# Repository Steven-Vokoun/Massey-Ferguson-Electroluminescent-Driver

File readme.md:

# Massey Ferguson Electroluminescent Driver
Based upon the Steve Pietkiewicz of LTC Electroluminescent Panel Power Supply in [Linear Technology Application Note 61](https://www.analog.com/media/en/technical-documentation/application-notes/an61fa.pdf) August 1994
Project never long term tested due to only having one Electroluminescent gauge left on the tractor which was cloudy so just decided to use 12V modern gauges.  Thought more were EL gauges, but they were just burned out 12v lamps.  Simply completed this to learn Kicad with a usedful project before moving on to more complex things.

## Features
- Adjustable Voltage and Frequency
> After searching everything on line could not find the specifications for this old of a tractor so made sure it was adjustable to fine tune brightness.
- Square wave output centered around 0
- Case with mounting points for zip ties
> Ended up mounting it to the vibration dampening mount that the voltage regulator was previously on.  Tractor has a internally regulated alternator so it was no longer needed.  It could also be attached to the bolt pattern on the existing EL driver instead.

## Known Issues
- +5V pin of the 555 timer not routed.  Fixed on board with a jumper wire
- resistor between the output of the 555 timer and the transistor needs a current limiting resistor between
- Potentiometer choices I ordered allowed for too large of a voltage swing which ended up bruning out my voltage regulator.  To fix this I used a generic boost converter I had lying around from 12v to 90v from that fit in the case as I did not want to wait on shipping of a new lienar regulator.  [Boost Converter](https://www.amazon.com/gp/product/B09P3MTC4J/ref=ppx_yo_dt_b_asin_title_o00_s01?ie=UTF8&psc=1).  I simply spliced this before the last diode in the multiiplier in order to inject the power directly.

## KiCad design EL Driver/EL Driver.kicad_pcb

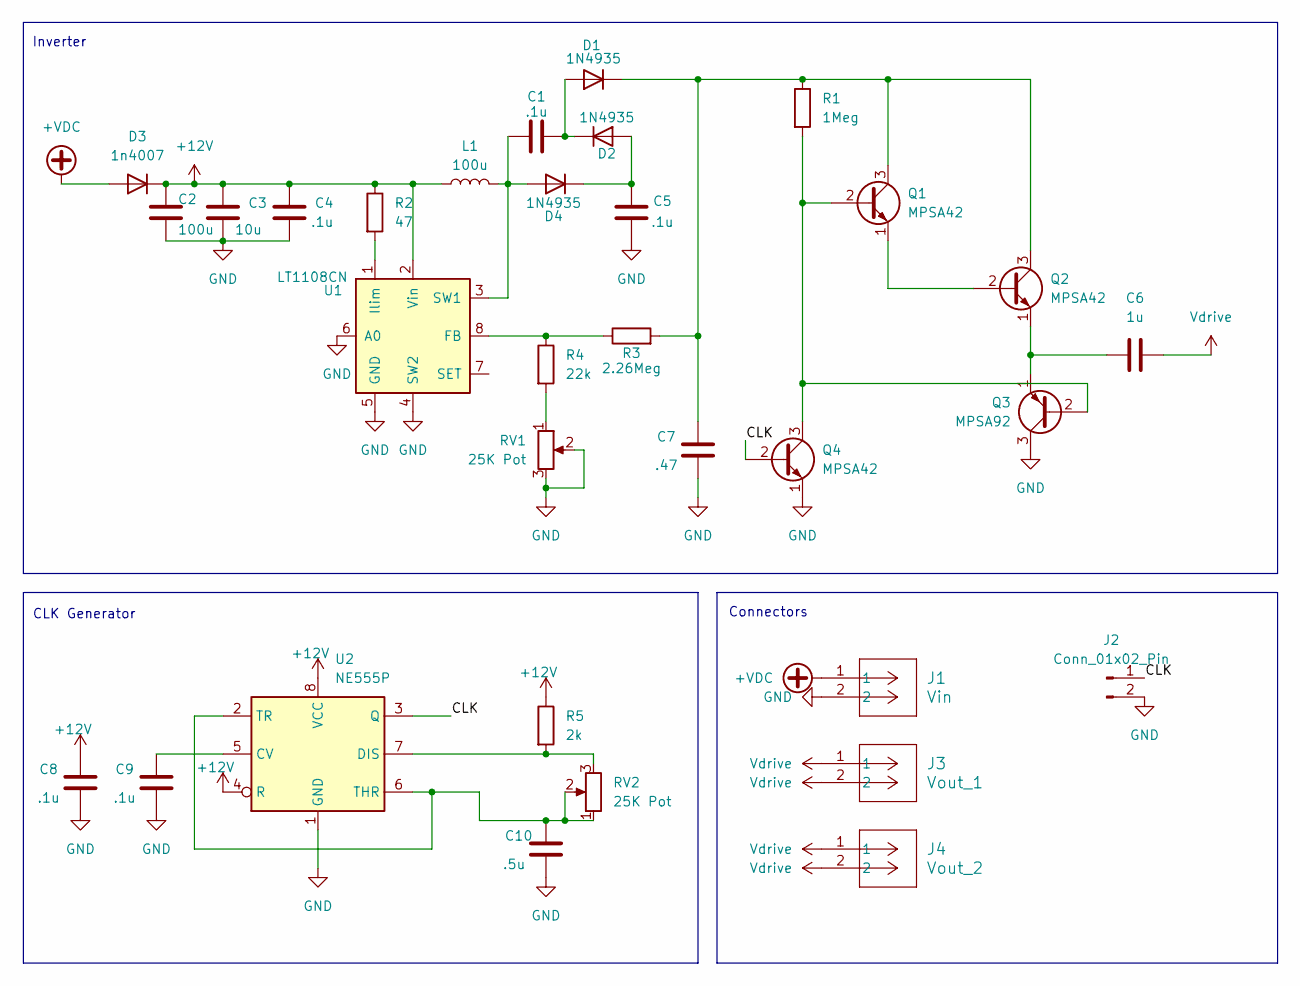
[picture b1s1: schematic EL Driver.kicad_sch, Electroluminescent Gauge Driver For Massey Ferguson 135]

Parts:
C1, C5: .1u; C_Rect_L7.2mm_W7.2mm_P5.00mm_FKS2_FKP2_MKS2_MKP2
C2: 100u; C_Radial_D8.0mm_H11.5mm_P3.50mm
C3: 10u; C_Disc_D5.1mm_W3.2mm_P5.00mm
C4, C8, C9: .1u; C_Disc_D5.1mm_W3.2mm_P5.00mm
C6: 1u; C_Radial_D6.3mm_H11.0mm_P2.50mm
C7: .47; C_Rect_L18.0mm_W9.0mm_P15.00mm_FKS3_FKP3
C10: .5u; C_Disc_D5.1mm_W3.2mm_P5.00mm
D1: 1N4935; DO-41
D2, D4: 1N4935; D_DO-41_SOD81_P7.62mm_Horizontal
D3: 1n4007; D_DO-41_SOD81_P7.62mm_Horizontal
J1: Vin; CONN2_1776493-2_TEC
J2: Conn_01x02_Pin; PinHeader_1x02_P2.54mm_Vertical
J3: Vout_1; CONN2_1776493-2_TEC
J4: Vout_2; CONN2_1776493-2_TEC
L1: 100u; L_Radial_D9.5mm_P5.00mm_Fastron_07HVP
Q1, Q2, Q4: MPSA42; TO-92_Inline
Q3: MPSA92; TO-92_Inline
R1: 1Meg; R_Axial_DIN0207_L6.3mm_D2.5mm_P7.62mm_Horizontal
R2: 47; R_Axial_DIN0207_L6.3mm_D2.5mm_P7.62mm_Horizontal
R3: 2.26Meg; R_Axial_DIN0207_L6.3mm_D2.5mm_P7.62mm_Horizontal
R4: 22k; R_Axial_DIN0207_L6.3mm_D2.5mm_P7.62mm_Horizontal
R5: 2k; R_Axial_DIN0207_L6.3mm_D2.5mm_P7.62mm_Horizontal
RV1, RV2: 25K Pot; TRIM_3362P-1-253LF
U1: LT1108CN; DIP-8_W7.62mm
U2: NE555P; DIP-8_W7.62mm

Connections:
+12V: C2.1, C3.1, C4.1, C8.1, D3.1 (K), L1.1, R2.1, R5.1, U1.2 (Vin), U2.4 (R), U2.8 (VCC)
+VDC: D3.2 (A), J1.1
/CLK: J2.1, Q4.2 (B), U2.3 (Q)
GND: C2.2, C3.2, C4.2, C5.2, C7.2, C8.2, C9.2, C10.2, J1.2, J2.2, Q3.3 (C), Q4.1 (E), RV1.2, RV1.3, U1.4 (SW2), U1.5 (GND), U1.6 (A0), U2.1 (GND)
unnamed: C1.2, D1.2 (A), D2.1 (K)
unnamed: C7.1, D1.1 (K), Q1.3 (C), Q2.3 (C), R1.1, R3.2
unnamed: C5.1, D2.2 (A), D4.1 (K)
unnamed: C1.1, D4.2 (A), L1.2, U1.3 (SW1)
unnamed: Q1.2 (B), Q3.2 (B), Q4.3 (C), R1.2
unnamed: Q1.1 (E), Q2.2 (B)
unnamed: C6.1, Q2.1 (E), Q3.1 (E)
unnamed: R4.2, RV1.1
unnamed: R3.1, R4.1, U1.8 (FB)
unnamed: R2.2, U1.1 (Ilim)
unnamed: C9.1, U2.5 (CV)
unnamed: R5.2, RV2.3, U2.7 (DIS)
unnamed: C10.1, RV2.1, RV2.2, U2.2 (TR), U2.6 (THR)
Vdrive: C6.2, J3.1, J3.2, J4.1, J4.2

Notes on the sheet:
CLK Generator
Inverter
Connectors

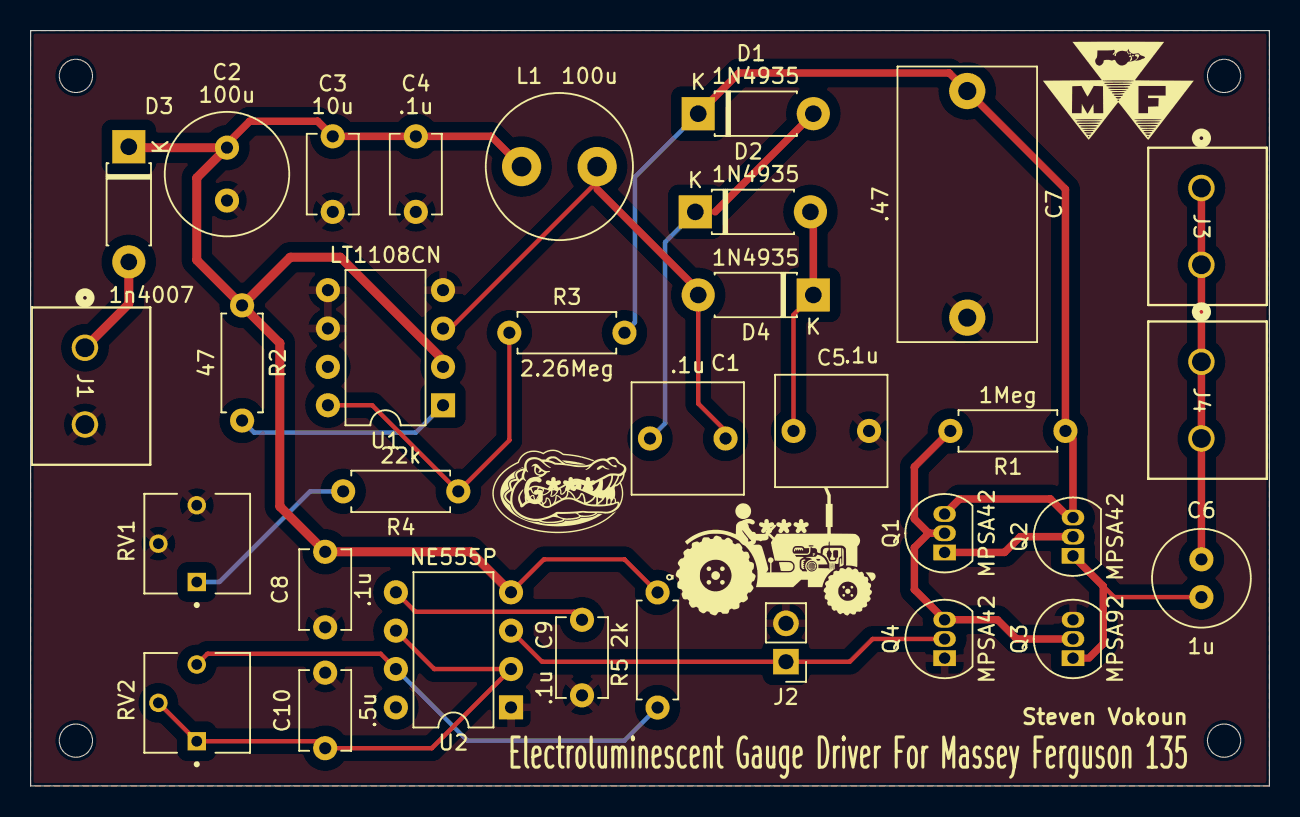
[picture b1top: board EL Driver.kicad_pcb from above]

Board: 2 copper layers, 82.0 x 50.0 mm, 32 parts (0 on the bottom side), 18 nets.

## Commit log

2024-07-01 First Version
